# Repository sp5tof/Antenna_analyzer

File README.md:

This is antenna analyzer project based on Jim KW4KD version. I added :
- TUNE mode (similar like VK5JST has)
- two hardware buttons to make interaction with a user (selecting mode, up/down frequency in TUNE mode etc.)
- supply voltage meter
- rechargeable accumulators based on cellphone’s battery
- support for popular TFT 1.8″ ST7735 display

Updates:

Harrie PE1JXI has provided improved PCB version of HF part (HF_PART_HARRIE)
and also SMD version (HF_part_SMD_version)
Thanks !

More informations can be found at http://sp5tof.qrz.pl

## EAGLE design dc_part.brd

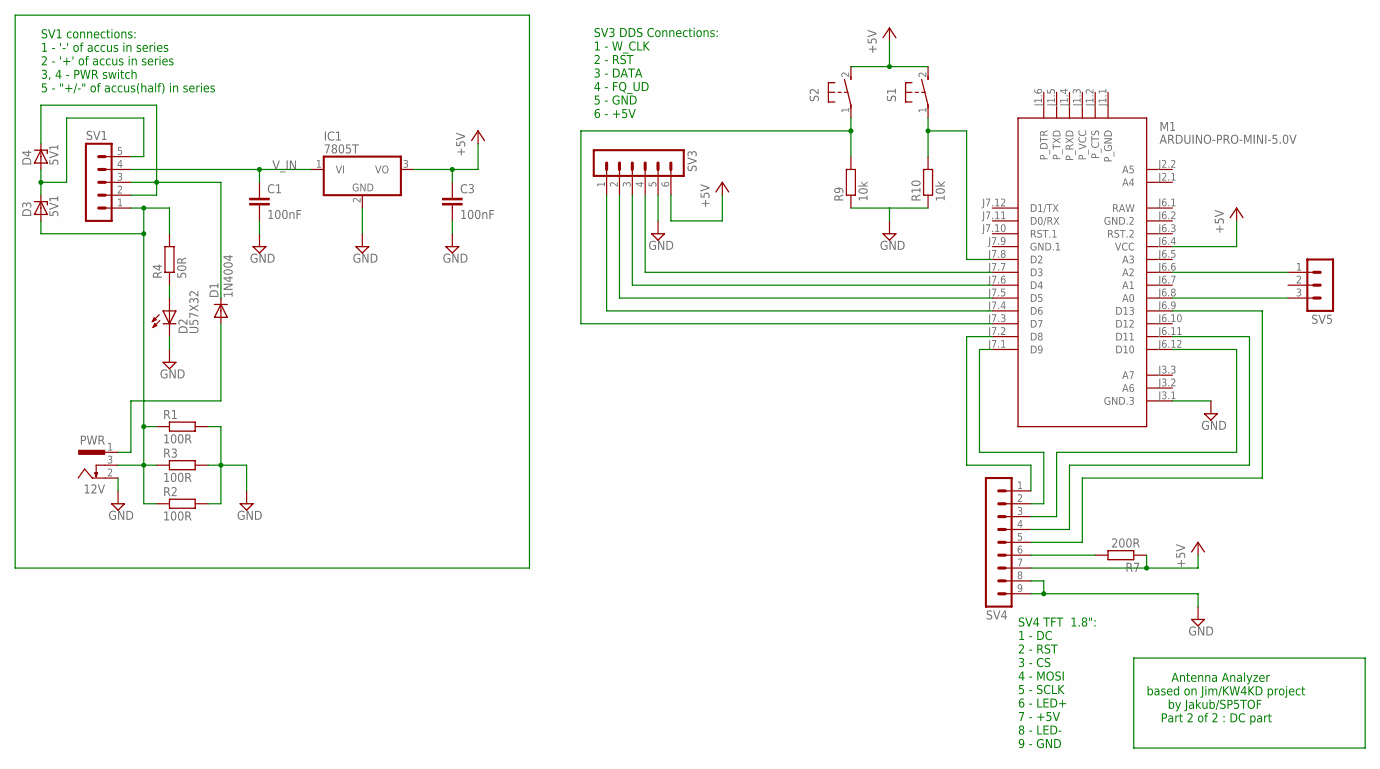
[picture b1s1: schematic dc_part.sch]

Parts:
C1, C3: 100nF; C050-024X044
D1: 1N4004; DO41-10
D2: U57X32
D3, D4: 5V1; ZDIO-5
IC1: 7805T; TO220H
M1: ARDUINO-PRO-MINI-5.0V; ARDUINO-PRO-MINI
PWR: 12V; 733980-62
R1, R2, R3: 100R; 0207/10
R4: 50R; 0207/10
R7: 200R; 0207/10
R9, R10: 10k; 0207/10
S1, S2: 31-XX; B3F-31XX
SV1: MA05-1
SV3: MA06-1
SV4: MA09-1
SV5: MA03-1

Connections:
+5V: C3.1, IC1.3 (VO), M1.J6.4 (VCC), R7.1, S1.2 (S), S2.2 (S), SV3.6, SV4.7
ACCU+: D1.C, D4.C, SV1.2, SV1.3
ACCU-: D3.A, PWR.3, R1.1, R2.1, R3.1, R4.2, SV1.1
GND: C1.2, C3.2, D2.K (C), IC1.2 (GND), M1.J3.1 (GND.3), PWR.2, R1.2, R2.2, R3.2, R9.1, R10.1, SV3.5, SV4.8, SV4.9
GND.1: M1.J7.9 (GND.1)
GND.2: M1.J6.2 (GND.2)
unnamed: R7.2, SV4.6
unnamed: D1.A, PWR.1
unnamed: M1.J7.2 (D8), SV4.1
unnamed: D2.A, R4.1
unnamed: D3.C, D4.A, SV1.5
unnamed: M1.J7.4 (D6), SV3.1
unnamed: M1.J7.5 (D5), SV3.2
unnamed: M1.J7.6 (D4), SV3.3
unnamed: M1.J7.7 (D3), SV3.4
unnamed: M1.J7.1 (D9), SV4.2
unnamed: M1.J6.12 (D10), SV4.3
unnamed: M1.J6.11 (D11), SV4.4
unnamed: M1.J6.9 (D13), SV4.5
unnamed: M1.J6.6 (A2), SV5.1
unnamed: M1.J6.8 (A0), SV5.3
unnamed: M1.J7.8 (D2), R10.2, S1.1
unnamed: M1.J7.3 (D7), R9.2, S2.1
RAW: M1.J6.1 (RAW)
V_IN: C1.1, IC1.1 (VI), SV1.4

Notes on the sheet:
SV1 connections: 1 - '-' of accus in series 2 - '+' of accus in series 3, 4 - PWR switch 5 - "+/-" of accus(half) in series
SV3 DDS Connections: 1 - W_CLK 2 - RST 3 - DATA 4 - FQ_UD 5 - GND 6 - +5V
SV4 TFT 1.8": 1 - DC 2 - RST 3 - CS 4 - MOSI 5 - SCLK 6 - LED+ 7 - +5V 8 - LED- 9 - GND
Antenna Analyzer based on Jim/KW4KD project by Jakub/SP5TOF Part 2 of 2 : DC part

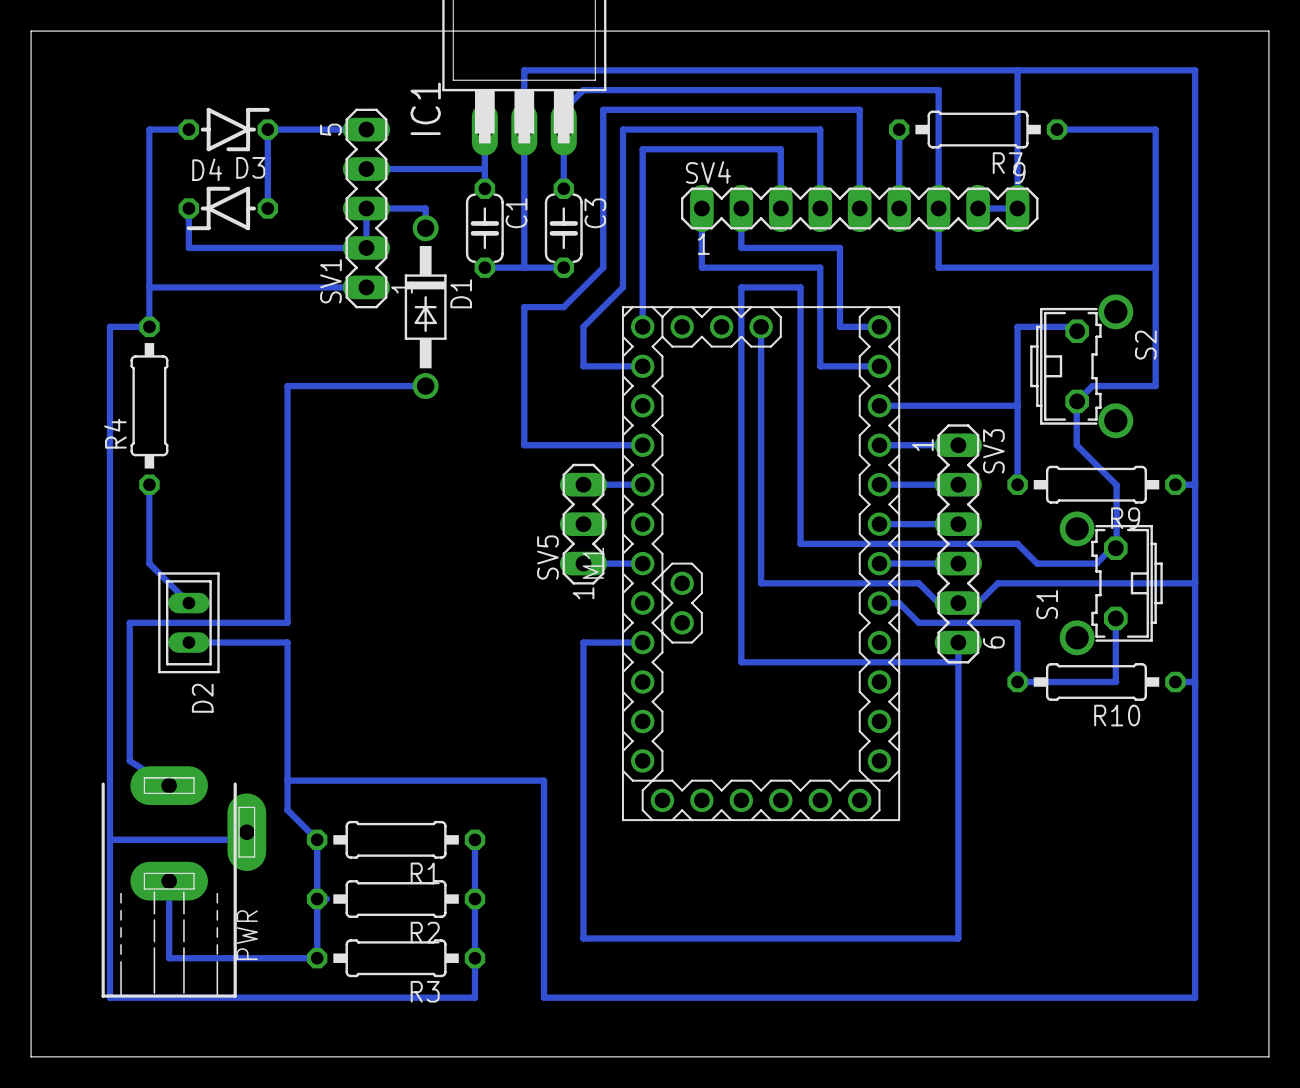
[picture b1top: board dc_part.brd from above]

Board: 2 copper layers, 79.7 x 66.0 mm, 22 parts (0 on the bottom side), 22 nets.

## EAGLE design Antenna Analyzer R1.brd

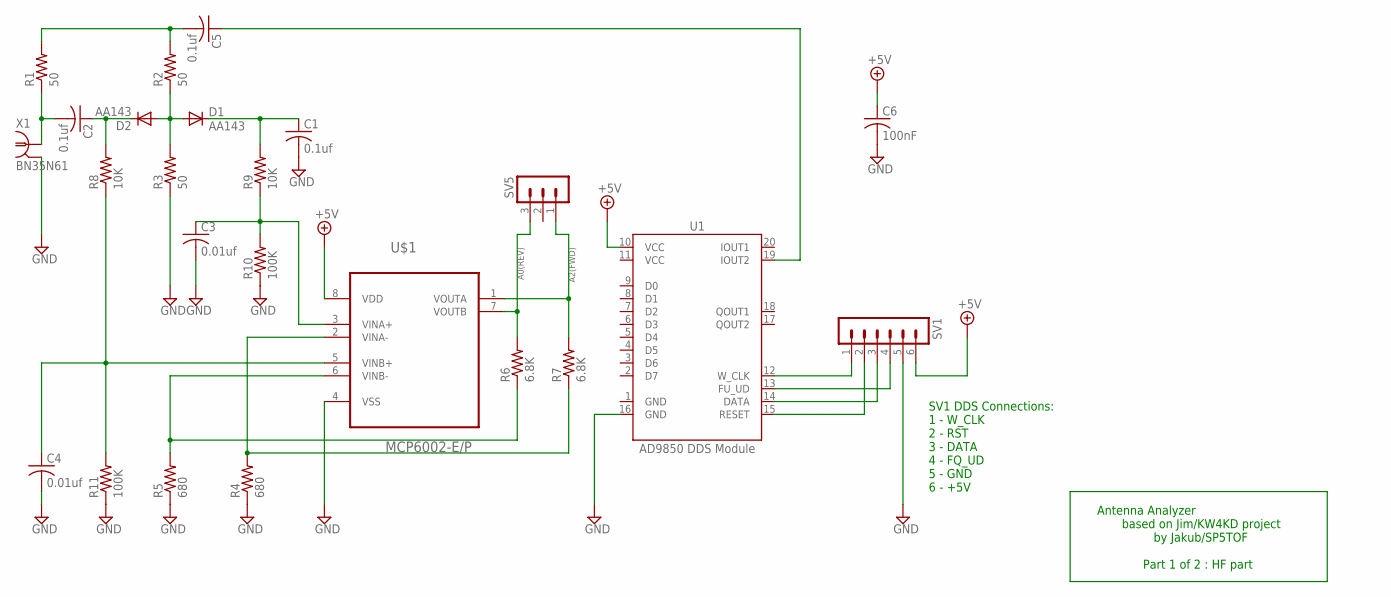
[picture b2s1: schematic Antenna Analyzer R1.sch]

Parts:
C1, C2, C5: 0.1uf; C050-025X075
C3, C4: 0.01uf; C050-025X075
C6: 100nF; C050-025X075
D1, D2: AA143; DO07
R1, R2, R3: 50; 0309/12
R4, R5: 680; 0309/12
R6, R7: 6.8K; 0309/12
R8, R9: 10K; 0309/12
R10, R11: 100K; 0309/12
SV1: MA06-1
SV5: MA03-1
U1: AD9850 DDS Module; DDS_AD9850
U$1: MCP6002-E/P; DIP254P762X533-8
X1: BN35N61; B35N61

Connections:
+5V: C6.1, SV1.6, U1.10 (VCC), U$1.8 (VDD)
A0(REV): R6.2, SV5.3, U$1.7 (VOUTB)
A2(FWD): R7.2, SV5.1, U$1.1 (VOUTA)
GND: C1.2, C3.2, C4.2, C6.2, R3.1, R4.1, R5.1, R10.1, R11.1, SV1.5, U1.1 (GND), U1.16 (GND), U$1.4 (VSS), X1.2, X1.3 (2), X1.4 (2), X1.5 (2)
unnamed: D1.A, D2.A, R2.1, R3.2
unnamed: C2.2, R1.1, X1.1
unnamed: C2.1, D2.C, R8.2
unnamed: C1.1, D1.C, R9.2
unnamed: C3.1, R9.1, R10.2, U$1.3 (VINA+)
unnamed: C5.2, R1.2, R2.2
unnamed: SV1.1, U1.12 (W_CLK)
unnamed: SV1.2, U1.15 (RESET)
unnamed: R5.2, R6.1, U$1.6 (VINB-)
unnamed: C4.1, R8.1, R11.2, U$1.5 (VINB+)
unnamed: R4.2, R7.1, U$1.2 (VINA-)
unnamed: C5.1, U1.19 (IOUT2)
unnamed: SV1.3, U1.14 (DATA)
unnamed: SV1.4, U1.13 (FU_UD)
VCC: U1.11 (VCC)

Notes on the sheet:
SV1 DDS Connections: 1 - W_CLK 2 - RST 3 - DATA 4 - FQ_UD 5 - GND 6 - +5V
Antenna Analyzer based on Jim/KW4KD project by Jakub/SP5TOF Part 1 of 2 : HF part

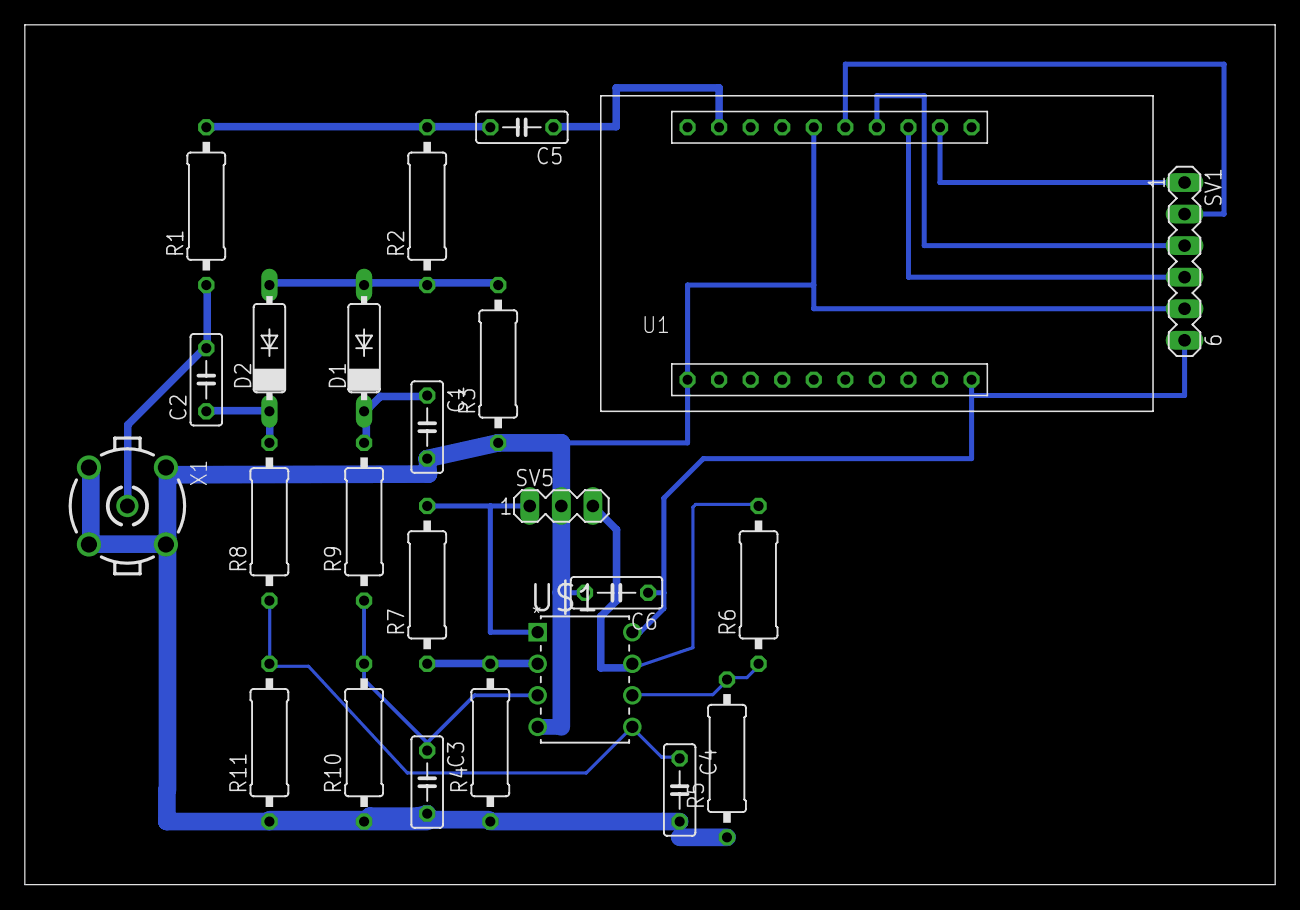
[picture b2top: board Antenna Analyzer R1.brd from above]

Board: 2 copper layers, 100.6 x 69.2 mm, 24 parts (0 on the bottom side), 18 nets.

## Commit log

2025-01-07 Add files via upload
    Arduino code
2025-01-07 Add files via upload
    Schema - DC part
2025-01-07 Add files via upload
    Schema - HF part
2025-01-07 Add files via upload
    Additional libraries required for Arduino IDE
2025-01-07 Add files via upload
    Eagle Schema
2025-01-07 Add files via upload
    Eagle schema - DC part
2025-01-07 Add files via upload
    Harrie PE1JXI has provided improved PCB version of HF part
2025-01-07 Add files via upload
    HF_part_SMD_version

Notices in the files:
parts and their libraries:
diy-modules: Released under the Creative Commons Attribution 4.0 International License: http://creativecommons.org/licenses/by/4.0
